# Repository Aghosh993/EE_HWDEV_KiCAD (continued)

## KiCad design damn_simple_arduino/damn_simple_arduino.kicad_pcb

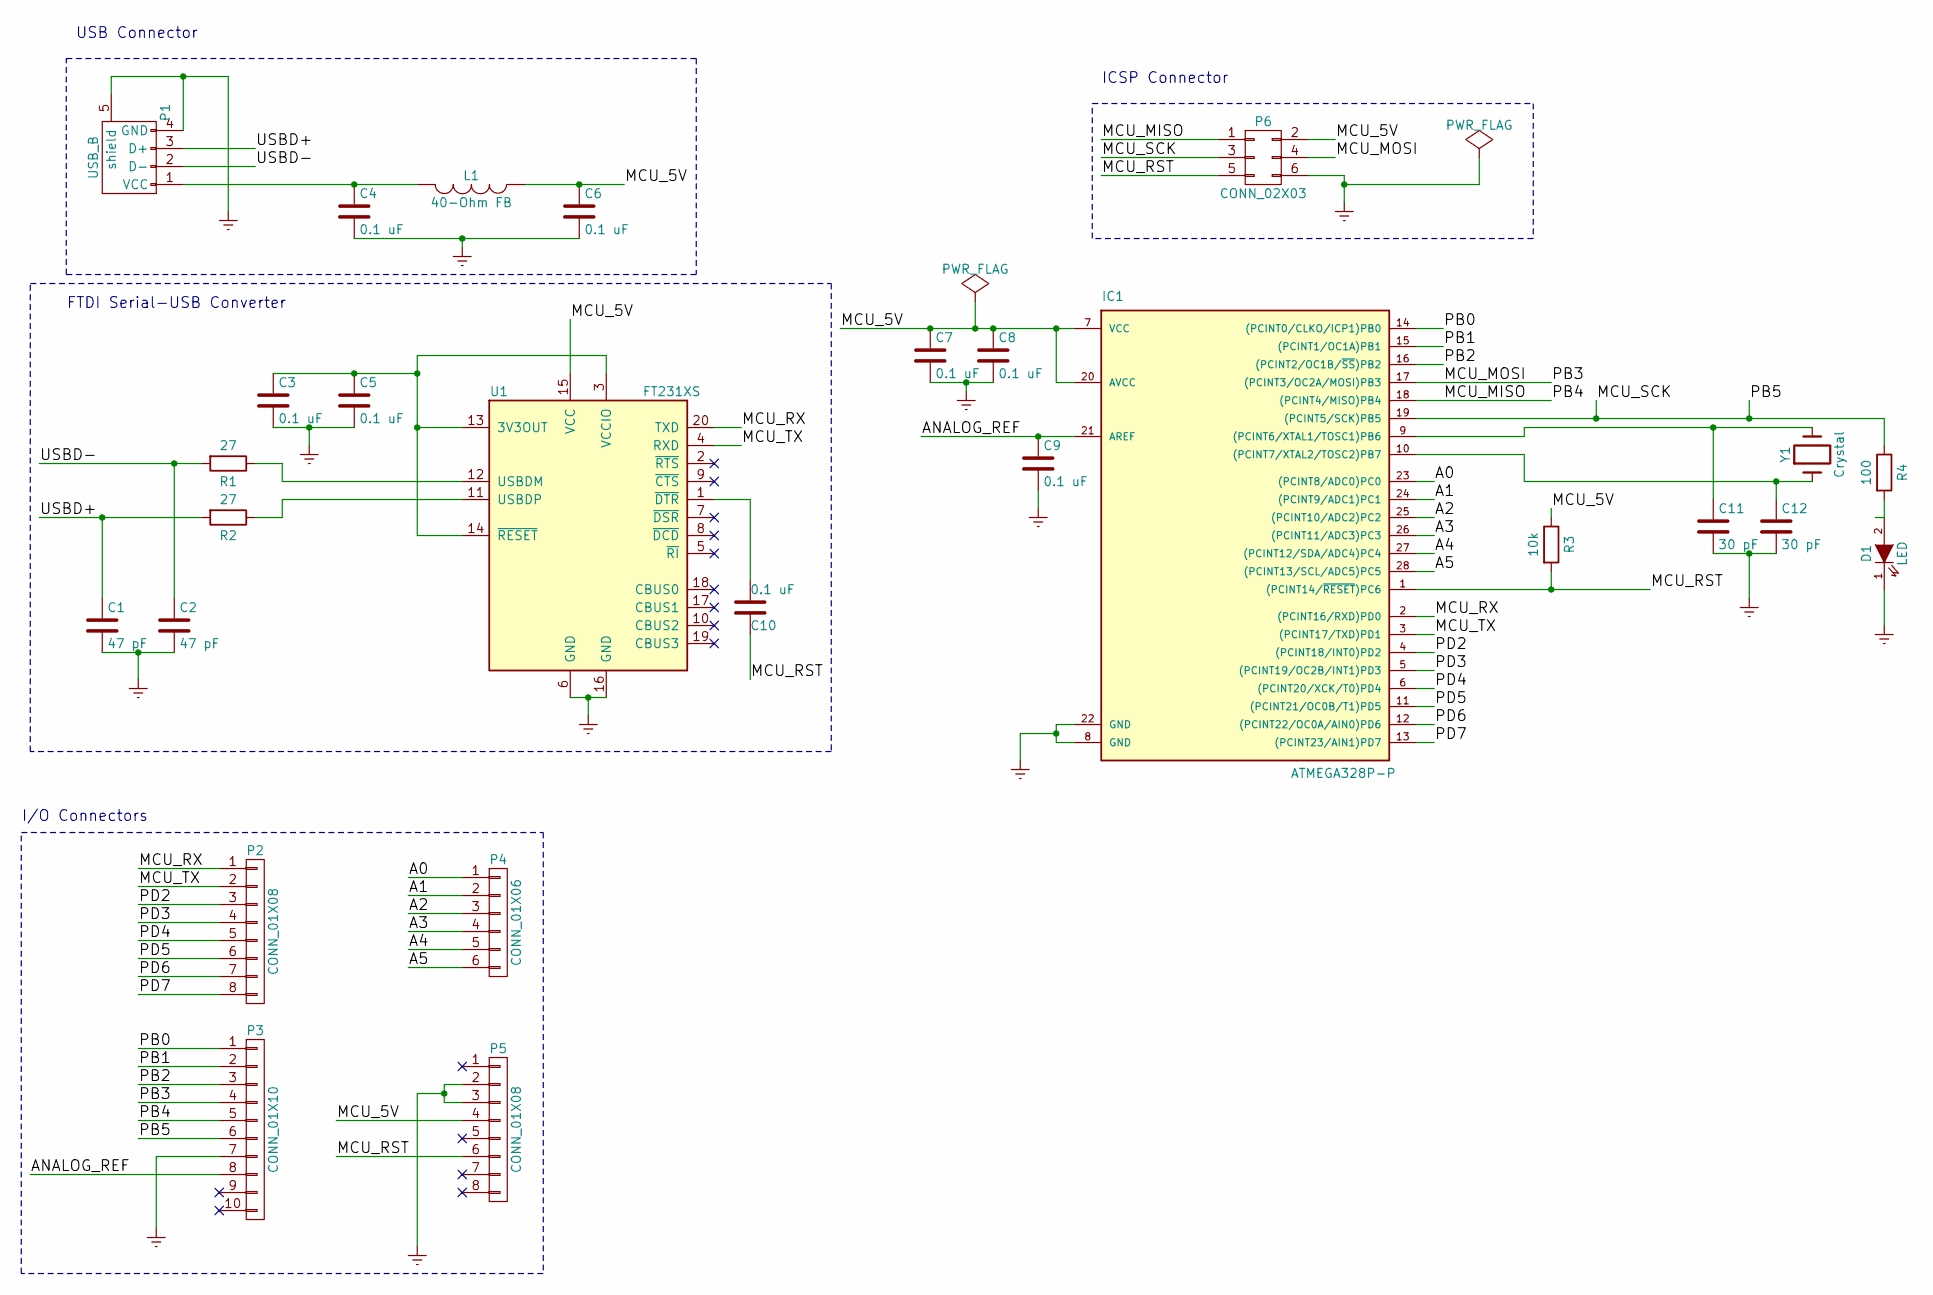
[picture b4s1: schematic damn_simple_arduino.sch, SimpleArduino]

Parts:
C1, C2: 47 pF; C_0603_HandSoldering
C3, C4, C5, C6, C7, C8, C9, C10: 0.1 uF; C_0603_HandSoldering
C11, C12: 30 pF; C_0402
D1: LED; LED-5MM
IC1: ATMEGA328P-P; DIP-28_W7.62mm
L1: 40-Ohm FB; C_0805_HandSoldering
P1: USB_B
P2, P5: CONN_01X08; Pin_Header_Straight_1x08
P3: CONN_01X10; Pin_Header_Straight_1x10
P4: CONN_01X06; Pin_Header_Straight_1x06
P6: CONN_02X03; Pin_Header_Straight_2x03
R1, R2: 27; R_0603_HandSoldering
R3: 10k; R_0603_HandSoldering
R4: 100; R_0603_HandSoldering
U1: FT231XS; SSOP-20-8.66x3.91_0.635mm
Y1: Crystal; Crystal_HC49-U_Vertical

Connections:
/A0: IC1.23 ((PCINT8/ADC0)PC0), P4.1
/A1: IC1.24 ((PCINT9/ADC1)PC1), P4.2
/A2: IC1.25 ((PCINT10/ADC2)PC2), P4.3
/A3: IC1.26 ((PCINT11/ADC3)PC3), P4.4
/A4: IC1.27 ((PCINT12/SDA/ADC4)PC4), P4.5
/A5: IC1.28 ((PCINT13/SCL/ADC5)PC5), P4.6
/ANALOG_REF: C9.1, IC1.21 (AREF), P3.8
/MCU_5V: C6.1, C7.1, C8.1, IC1.7 (VCC), IC1.20 (AVCC), L1.1, P5.4, P6.2, R3.1, U1.15 (VCC)
/MCU_MISO: IC1.18 ((PCINT4/MISO)PB4), P3.5, P6.1
/MCU_MOSI: IC1.17 ((PCINT3/OC2A/MOSI)PB3), P3.4, P6.4
/MCU_RST: C10.1, IC1.1 ((PCINT14/~RESET~)PC6), P5.6, P6.5, R3.2
/MCU_RX: IC1.2 ((PCINT16/RXD)PD0), P2.1, U1.20 (TXD)
/MCU_SCK: IC1.19 ((PCINT5/SCK)PB5), P3.6, P6.3, R4.1
/MCU_TX: IC1.3 ((PCINT17/TXD)PD1), P2.2, U1.4 (RXD)
/PB0: IC1.14 ((PCINT0/CLKO/ICP1)PB0), P3.1
/PB1: IC1.15 ((PCINT1/OC1A)PB1), P3.2
/PB2: IC1.16 ((PCINT2/OC1B/~SS~)PB2), P3.3
/PD2: IC1.4 ((PCINT18/INT0)PD2), P2.3
/PD3: IC1.5 ((PCINT19/OC2B/INT1)PD3), P2.4
/PD4: IC1.6 ((PCINT20/XCK/T0)PD4), P2.5
/PD5: IC1.11 ((PCINT21/OC0B/T1)PD5), P2.6
/PD6: IC1.12 ((PCINT22/OC0A/AIN0)PD6), P2.7
/PD7: IC1.13 ((PCINT23/AIN1)PD7), P2.8
/USBD+: C1.1, P1.3 (D+), R2.2
/USBD-: C2.1, P1.2 (D-), R1.2
Earth: C1.2, C2.2, C3.2, C4.2, C5.2, C6.2, C7.2, C8.2, C9.2, C11.2, C12.2, D1.1 (K), IC1.8 (GND), IC1.22 (GND), P1.4 (GND), P1.5 (shield), P3.7, P5.2, P5.3, P6.6, U1.6 (GND), U1.16 (GND)
unnamed: C3.1, C5.1, U1.3 (VCCIO), U1.13 (3V3OUT), U1.14 (~RESET)
unnamed: C4.1, L1.2, P1.1 (VCC)
unnamed: C10.2, U1.1 (~DTR)
unnamed: C11.1, IC1.9 ((PCINT6/XTAL1/TOSC1)PB6), Y1.2
unnamed: C12.1, IC1.10 ((PCINT7/XTAL2/TOSC2)PB7), Y1.1
unnamed: D1.2 (A), R4.2
unnamed: R1.1, U1.12 (USBDM)
unnamed: R2.1, U1.11 (USBDP)

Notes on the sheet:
ICSP Connector
USB Connector
FTDI Serial-USB Converter
I/O Connectors

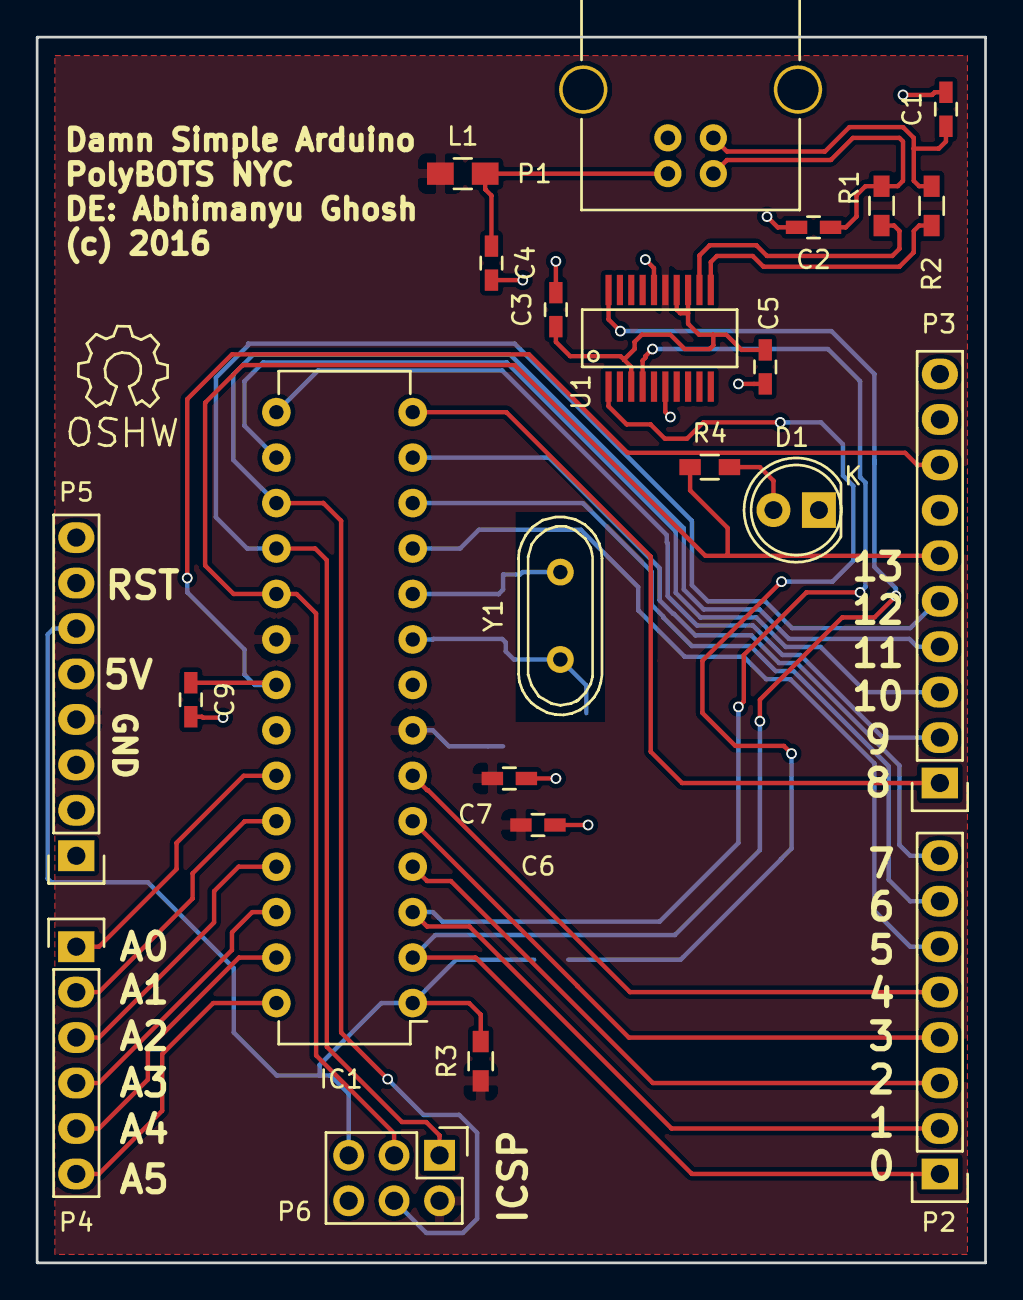
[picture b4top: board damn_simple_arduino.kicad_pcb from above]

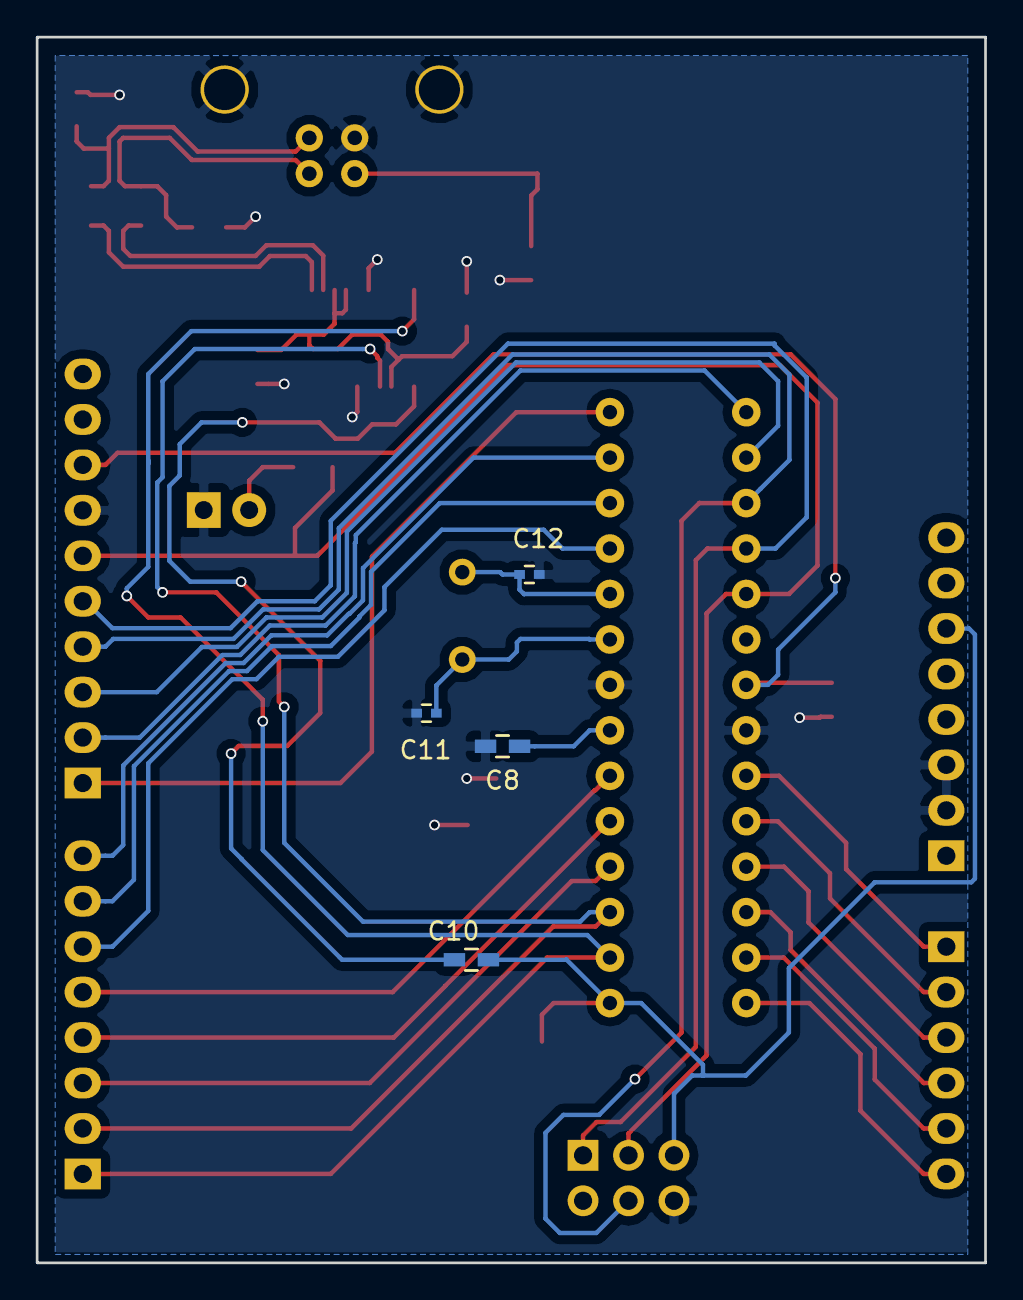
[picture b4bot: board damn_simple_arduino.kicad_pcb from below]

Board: 2 copper layers, 53.0 x 68.5 mm, 27 parts (4 on the bottom side), 34 nets.

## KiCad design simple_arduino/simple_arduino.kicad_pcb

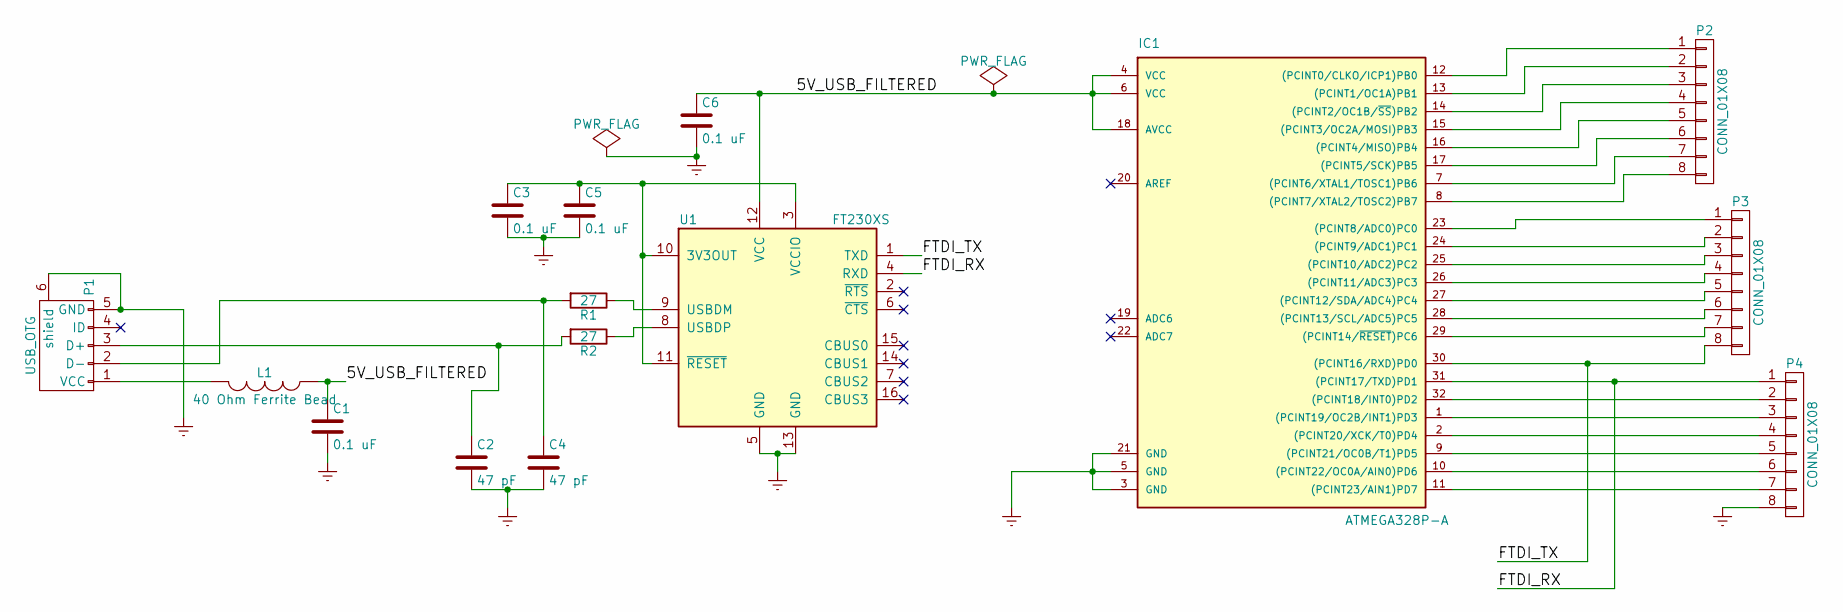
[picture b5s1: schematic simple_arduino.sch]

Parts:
C1, C3, C5, C6: 0.1 uF; C_0603_HandSoldering
C2, C4: 47 pF; C_0603_HandSoldering
IC1: ATMEGA328P-A; TQFP-32_7x7mm_Pitch0.8mm
L1: 40 Ohm Ferrite Bead; C_0805_HandSoldering
P1: USB_OTG; USB_Micro-B
P2, P3, P4: CONN_01X08; Socket_Strip_Straight_1x08
R1, R2: 27; R_0603_HandSoldering
U1: FT230XS; SSOP-16_3.9x4.9mm_Pitch0.635mm

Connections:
/5V_USB_FILTERED: C1.1, C6.1, IC1.4 (VCC), IC1.6 (VCC), IC1.18 (AVCC), L1.1, U1.12 (VCC)
/FTDI_RX: IC1.31 ((PCINT17/TXD)PD1), P4.1, U1.4 (RXD)
/FTDI_TX: IC1.30 ((PCINT16/RXD)PD0), P3.8, U1.1 (TXD)
Earth: C1.2, C2.2, C3.2, C4.2, C5.2, C6.2, IC1.3 (GND), IC1.5 (GND), IC1.21 (GND), P1.5 (GND), P1.6 (shield), P4.8, U1.5 (GND), U1.13 (GND)
unnamed: C2.1, P1.3 (D+), R2.2
unnamed: C3.1, C5.1, U1.3 (VCCIO), U1.10 (3V3OUT), U1.11 (~RESET)
unnamed: C4.1, P1.2 (D-), R1.2
unnamed: IC1.1 ((PCINT19/OC2B/INT1)PD3), P4.3
unnamed: IC1.2 ((PCINT20/XCK/T0)PD4), P4.4
unnamed: IC1.7 ((PCINT6/XTAL1/TOSC1)PB6), P2.7
unnamed: IC1.8 ((PCINT7/XTAL2/TOSC2)PB7), P2.8
unnamed: IC1.9 ((PCINT21/OC0B/T1)PD5), P4.5
unnamed: IC1.10 ((PCINT22/OC0A/AIN0)PD6), P4.6
unnamed: IC1.11 ((PCINT23/AIN1)PD7), P4.7
unnamed: IC1.12 ((PCINT0/CLKO/ICP1)PB0), P2.1
unnamed: IC1.13 ((PCINT1/OC1A)PB1), P2.2
unnamed: IC1.14 ((PCINT2/OC1B/~SS~)PB2), P2.3
unnamed: IC1.15 ((PCINT3/OC2A/MOSI)PB3), P2.4
unnamed: IC1.16 ((PCINT4/MISO)PB4), P2.5
unnamed: IC1.17 ((PCINT5/SCK)PB5), P2.6
unnamed: IC1.23 ((PCINT8/ADC0)PC0), P3.1
unnamed: IC1.24 ((PCINT9/ADC1)PC1), P3.2
unnamed: IC1.25 ((PCINT10/ADC2)PC2), P3.3
unnamed: IC1.26 ((PCINT11/ADC3)PC3), P3.4
unnamed: IC1.27 ((PCINT12/SDA/ADC4)PC4), P3.5
unnamed: IC1.28 ((PCINT13/SCL/ADC5)PC5), P3.6
unnamed: IC1.29 ((PCINT14/~RESET~)PC6), P3.7
unnamed: IC1.32 ((PCINT18/INT0)PD2), P4.2
unnamed: L1.2, P1.1 (VCC)
unnamed: R1.1, U1.9 (USBDM)
unnamed: R2.1, U1.8 (USBDP)

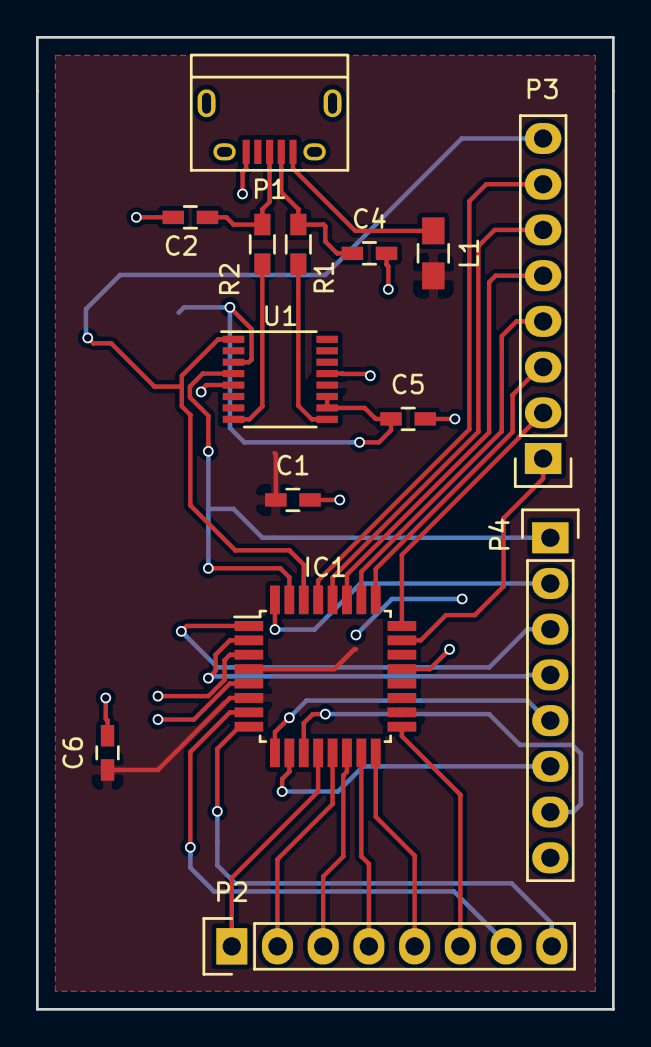
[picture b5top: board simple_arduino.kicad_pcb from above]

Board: 2 copper layers, 32.0 x 54.0 mm, 15 parts (1 on the bottom side), 31 nets.

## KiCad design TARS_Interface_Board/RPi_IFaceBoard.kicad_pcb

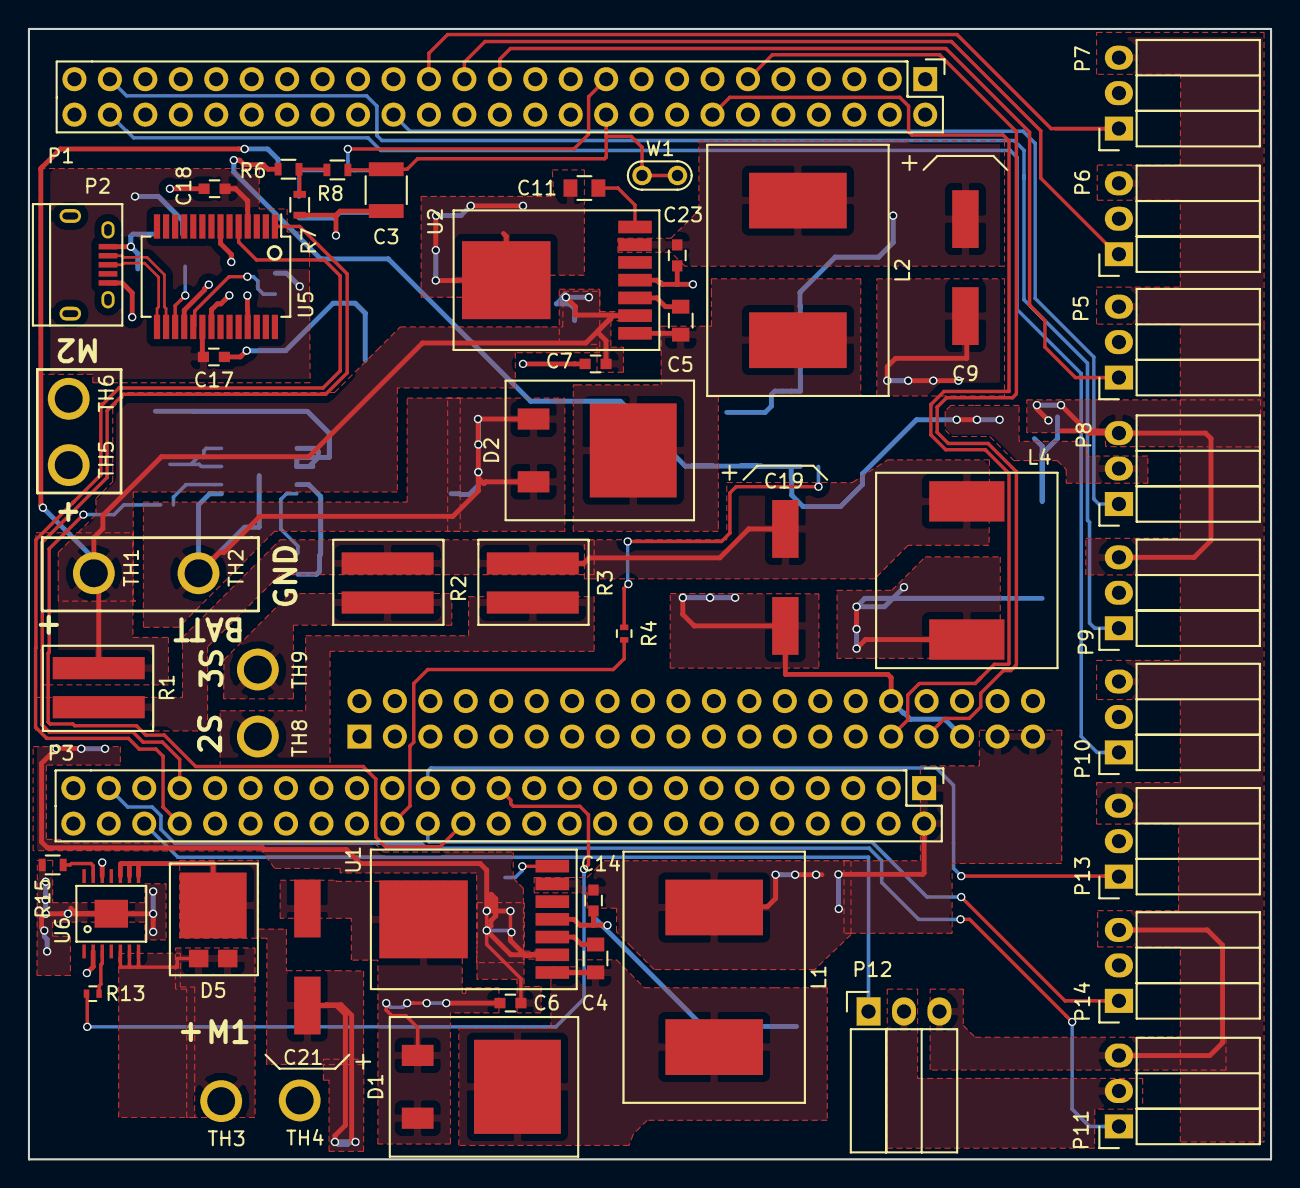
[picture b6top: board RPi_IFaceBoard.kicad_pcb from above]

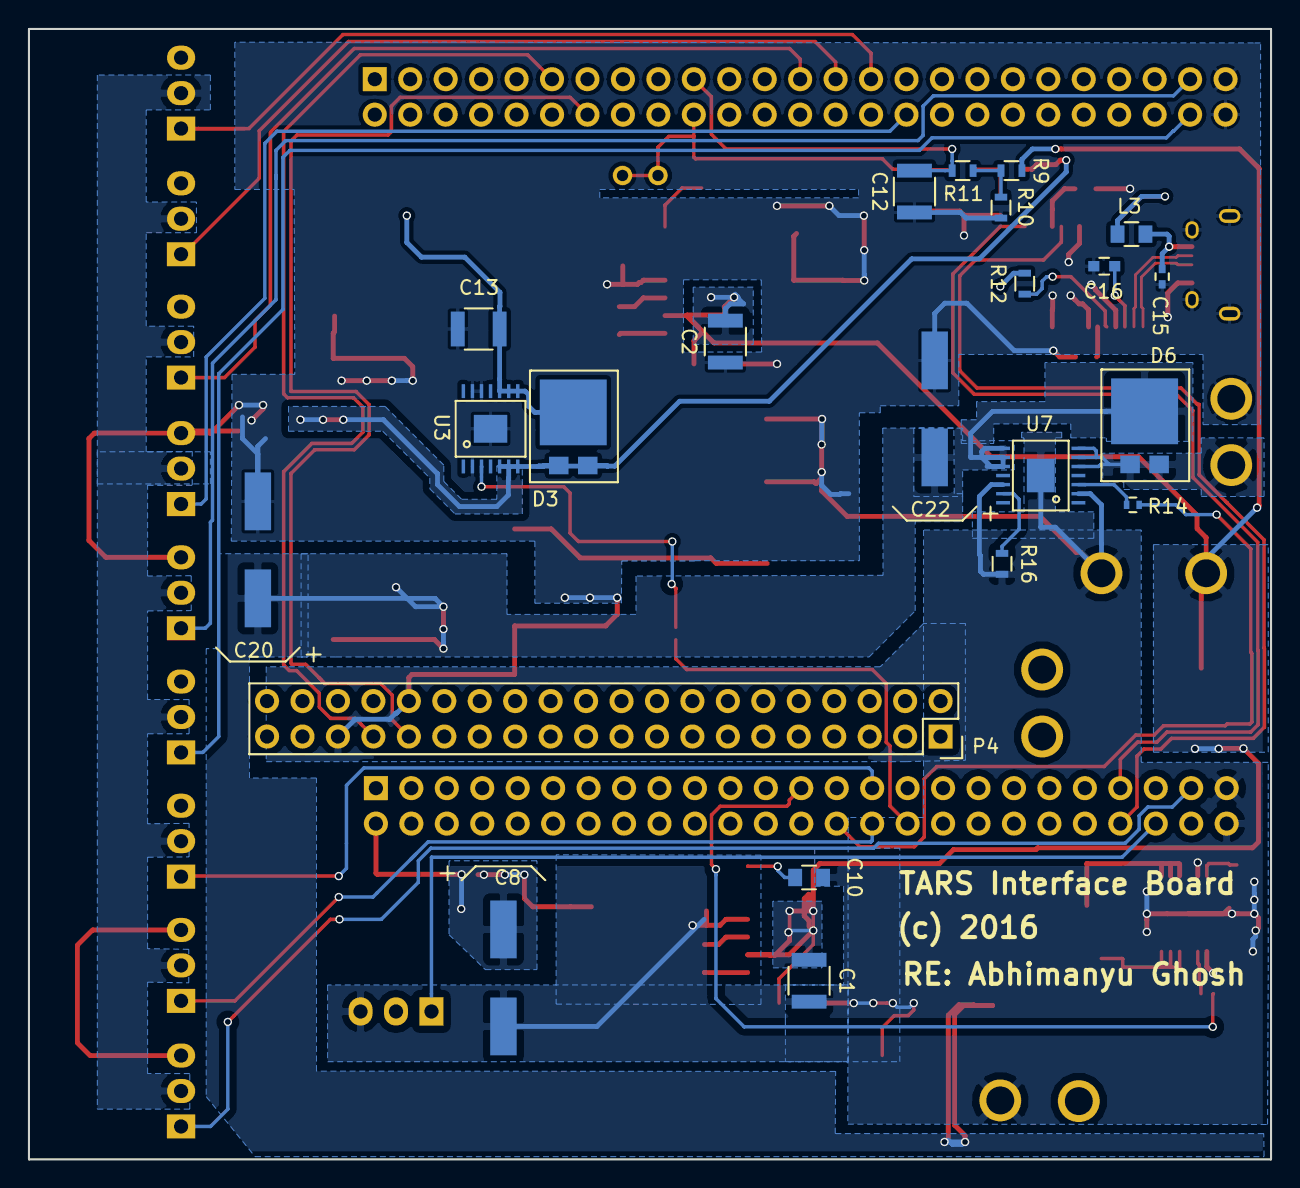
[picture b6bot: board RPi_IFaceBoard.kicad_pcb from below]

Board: 2 copper layers, 89.0 x 81.0 mm, 76 parts (22 on the bottom side), 49 nets.

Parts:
C1, C2, C3, C12, C13: 10 uF; C_1210
C4, C5: 10 nF; C_0805
C6, C7, C14, C23: 1.0 uF; C_0603
C8, C9, C21, C22: 120 uF; Radial_SMD_8mm
C10, C11: 0.27 uF; C_0805
C15: 10 nF; C_0402
C16, C17, C18: 0.1 uF; C_0603
C19, C20: 82 uF; Radial_SMD_8mm
D1, D2: Vrrm=40.0V,Vf=510.0 mV; DPAK_TO252AA_CUSTOM
D3, D5, D6: SCHDPAK; TO277A
L1, L2: 6.5 uH, 18 mOhm; SRR1208
L3: 40 Ohm FB; C_0805
L4: 15 uH; INDUCTOR_SMD_WURTH_5.4X2.9PADS_9.9SPACE
P1, P3: CONN_02X25; Socket_Strip_Straight_2x25
P2: USB_OTG; USB_Micro-B
P4: CONN_02X20; Socket_Strip_Straight_2x20
P5, P6, P7, P8, P9, P10, P11, P12, P13, P14: CONN_01X03; Socket_Strip_Angled_1x03
R1: 0; RES_RCL1225
R2, R3: 0 DNP; RES_RCL1225
R4, R13, R14: 3.3K; R_0402
R6: 2.2K; R_0603
R7, R10: 1.1K; R_0603
R8, R11: 100; R_0603
R9: 6.65K; R_0603
R12: 10K; R_0603
R15, R16: 499; R_0603
TH1, TH2, TH3, TH4, TH5, TH6, TH8, TH9: PTH
U1, U2: LM22679; TI_TO-263
U3, U6, U7: TPS1H100AQPWPRQ1; PowerPAD_14pin_EP
U5: FT232RL; SSOP-28_5.3x10.2mm_Pitch0.65mm
W1: TEST_1P; Test_Point

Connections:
+5V: C8.1, C14.1, L1.2, P3.1, P3.2, P4.37, P4.39, U1.6
/DCMotor_Quarter_HBridges/AS_PWR: C19.1, L4.2, R1.1, R2.1, R3.1
/DCMotor_Quarter_HBridges/MOTOR0_OUT: D5.1, D5.3, TH3.1, U6.5, U6.6, U6.7
/DCMotor_Quarter_HBridges/MOTOR0_PWM: P3.25, R13.2
/DCMotor_Quarter_HBridges/MOTOR1_OUT: D6.1, D6.3, TH5.1, U7.5, U7.6, U7.7
/DCMotor_Quarter_HBridges/MOTOR1_PWM: P3.28, R14.2
/DCMotor_Quarter_HBridges/VBAT_FLT: C20.1, C21.1, C22.1, D5.2, D6.2, L4.1, U6.8, U6.9, U6.10, U7.8, U7.9, U7.10
/DebugFTDI/RX: P3.44, U5.5
/DebugFTDI/TX: P3.43, U5.1
/DebugFTDI/USBD+: P2.3, U5.15
/DebugFTDI/USBD-: P2.2, U5.16
/DebugFTDI/VUSB: C15.1, L3.2, P2.1
/DebugFTDI/VUSB_FLT: C17.1, C18.1, L3.1, R12.2, U5.4, U5.20
/PWM0: P1.25, P5.1
/PWM1: P1.27, P6.1
/PWM2: P1.29, P7.1
/PWM3: P1.32, P8.1
/PWM4: P1.47, P9.1
/PWM5: P1.48, P10.1
/PWM6: P3.47, P11.1
/PWM7: P3.46, P12.1
/PWM8: P3.29, P13.1
/PWM9: P3.30, P14.1
/PowerSupplies/SERVO_PWR_EN: P3.32, R4.2
/PowerSupplies/SERVO_PWR_FB: C3.1, P1.20, R8.1, W1.1
/PowerSupplies/SRV_5V_OUT: D3.1, D3.3, P5.2, P6.2, P7.2, P8.2, P9.2, P10.2, P11.2, P12.2, P13.2, P14.2, R6.1, U3.5, U3.6, U3.7
/PowerSupplies/SRV_5V_SW_UPSTREAM: C9.1, C13.1, C23.1, D3.2, L2.2, U2.6, U3.8, U3.9, U3.10
/PowerSupplies/SW_OUT: C4.2, D1.1, L1.1, U1.1
/PowerSupplies/SW_OUT2: C5.2, D2.1, L2.1, U2.1
/PowerSupplies/VBAT: C1.1, C2.1, C6.1, C7.1, R1.2, R9.1, TH1.1, U1.2, U2.2
/PowerSupplies/VBAT_FB: C12.1, P1.19, R11.1
/RX_PI: P1.11, P4.33
/TX_PI: P1.14, P4.31
/VBAT_2S: R3.2, TH8.1
/VBAT_3S: R2.2, TH9.1
Earth: C1.2, C2.2, C3.2, C6.2, C7.2, C8.2, C9.2, C10.2, C11.2, C12.2, C13.2, C14.2, C15.2, C16.2, C17.2, C18.2, C19.2, C20.2, C21.2, C22.2, C23.2, D1.2, D2.2, P1.49, P1.50, P2.5, P2.6, P3.49, P3.50, P4.32, P4.35, P5.3, P6.3, P7.3, P8.3, P9.3, P10.3, P11.3, P12.3, P13.3, P14.3, R7.2, R10.2, R15.2, R16.2, TH2.1, TH4.1, TH6.1, U1.4, U1.8, U2.4, U2.8, U3.2, U3.12, U3.13, U5.7, U5.18, U5.21, U5.25, U6.2, U6.12, U7.2, U7.12
unnamed: C4.1, U1.3
unnamed: C5.1, U2.3
unnamed: C10.1, U1.7
unnamed: C11.1, U2.7
unnamed: C16.1, U5.17
unnamed: R4.1, U3.3
unnamed: R6.2, R7.1, R8.2
unnamed: R9.2, R10.1, R11.2
unnamed: R12.1, U5.19
unnamed: R13.1, U6.3
unnamed: R14.1, U7.3
unnamed: R15.1, U6.13
unnamed: R16.1, U7.13

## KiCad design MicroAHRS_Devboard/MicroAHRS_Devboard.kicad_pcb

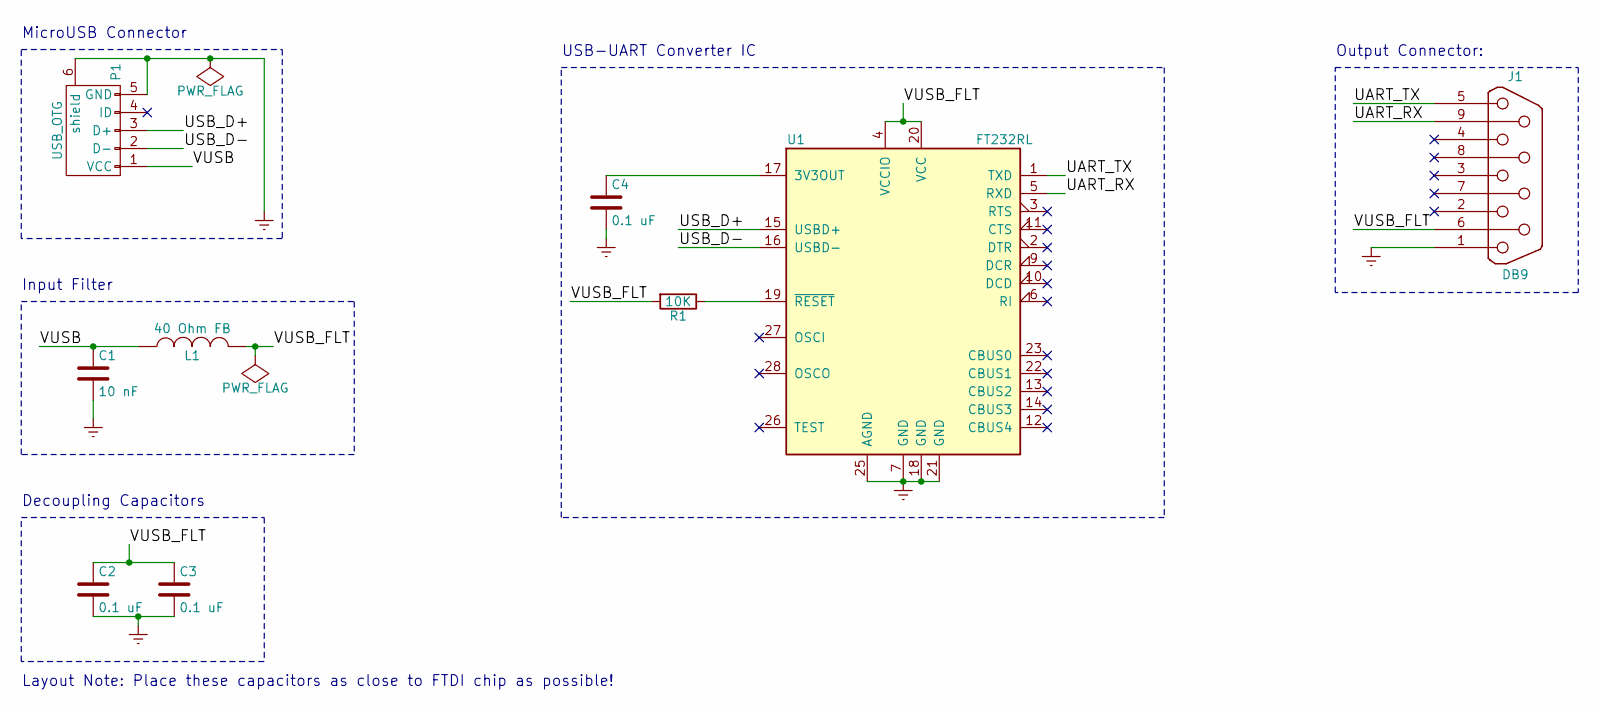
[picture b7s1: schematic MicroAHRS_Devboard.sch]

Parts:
C1: 10 nF; C_0402
C2, C3, C4: 0.1 uF; C_0603
J1: DB9; DB9MC
L1: 40 Ohm FB; C_0805
P1: USB_OTG; USB_Micro-B
R1: 10K; R_0603
U1: FT232RL; SSOP-28_5.3x10.2mm_Pitch0.65mm

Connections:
/UART_RX: J1.9, U1.5 (RXD)
/UART_TX: J1.5, U1.1 (TXD)
/USB_D+: P1.3 (D+), U1.15 (USBD+)
/USB_D-: P1.2 (D-), U1.16 (USBD-)
/VUSB: C1.1, L1.1, P1.1 (VCC)
/VUSB_FLT: C2.1, C3.1, J1.6, L1.2, R1.2, U1.4 (VCCIO), U1.20 (VCC)
Earth: C1.2, C2.2, C3.2, C4.2, J1.1, P1.5 (GND), P1.6 (shield), U1.7 (GND), U1.18 (GND), U1.21 (GND), U1.25 (AGND)
unnamed: C4.1, U1.17 (3V3OUT)
unnamed: R1.1, U1.19 (~RESET~)

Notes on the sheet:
MicroUSB Connector
Input Filter
Decoupling Capacitors
Layout Note: Place these capacitors as close to FTDI chip as possible!
Output Connector:
USB-UART Converter IC

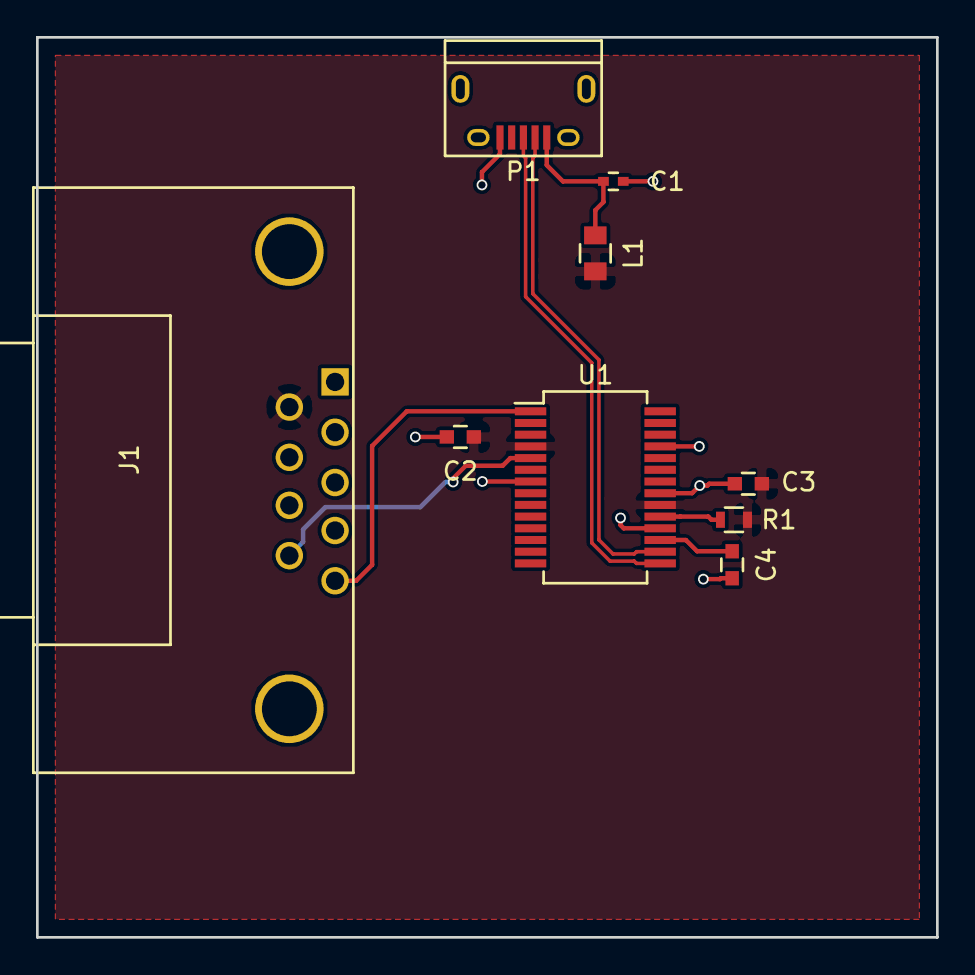
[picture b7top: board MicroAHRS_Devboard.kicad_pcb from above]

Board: 2 copper layers, 50.0 x 50.0 mm, 9 parts (0 on the bottom side), 9 nets.

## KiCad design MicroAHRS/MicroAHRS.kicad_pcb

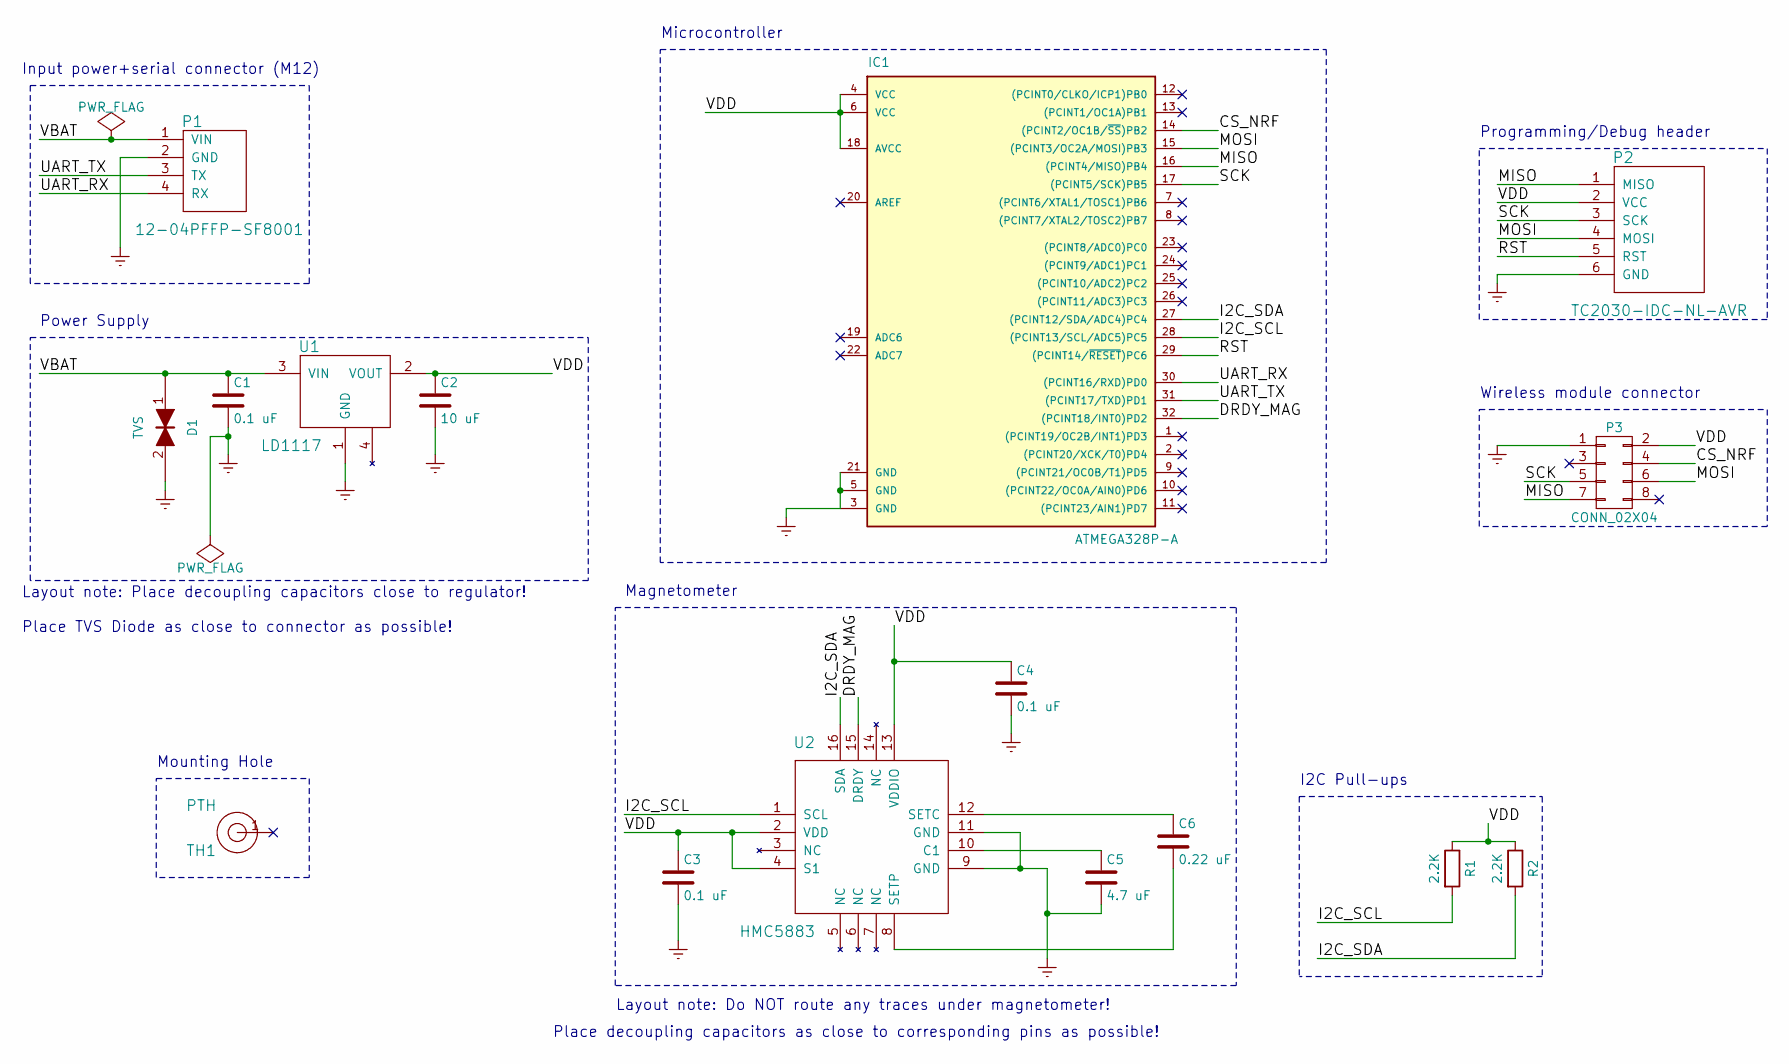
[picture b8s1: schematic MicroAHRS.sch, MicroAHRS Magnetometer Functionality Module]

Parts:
C1, C3, C4: 0.1 uF; C_0402
C2: 10 uF; C_0805
C5: 4.7 uF; C_1210
C6: 0.22 uF; C_0402
D1: TVS; TVS_0603
IC1: ATMEGA328P-A; TQFP-32_7x7mm_Pitch0.8mm
P1: 12-04PFFP-SF8001
P2: TC2030-IDC-NL-AVR
P3: CONN_02X04; Socket_Strip_Straight_2x04
R1, R2: 2.2K; R_0603
TH1: PTH; MountingHole_3mm
U1: LD1117; SOT-223
U2: HMC5883; LCC16

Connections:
/CS_NRF: IC1.14 ((PCINT2/OC1B/~SS~)PB2), P3.4
/DRDY_MAG: IC1.32 ((PCINT18/INT0)PD2), U2.15 (DRDY)
/I2C_SCL: IC1.28 ((PCINT13/SCL/ADC5)PC5), R1.2, U2.1 (SCL)
/I2C_SDA: IC1.27 ((PCINT12/SDA/ADC4)PC4), R2.2, U2.16 (SDA)
/MISO: IC1.16 ((PCINT4/MISO)PB4), P2.1 (MISO), P3.7
/MOSI: IC1.15 ((PCINT3/OC2A/MOSI)PB3), P2.4 (MOSI), P3.6
/RST: IC1.29 ((PCINT14/~RESET~)PC6), P2.5 (RST)
/SCK: IC1.17 ((PCINT5/SCK)PB5), P2.3 (SCK), P3.5
/UART_RX: IC1.30 ((PCINT16/RXD)PD0), P1.4 (RX)
/UART_TX: IC1.31 ((PCINT17/TXD)PD1), P1.3 (TX)
/VBAT: C1.1, D1.1, P1.1 (VIN), U1.3 (VIN)
/VDD: C2.1, C3.1, C4.1, IC1.4 (VCC), IC1.6 (VCC), IC1.18 (AVCC), P2.2 (VCC), P3.2, R1.1, R2.1, U1.2 (VOUT), U2.2 (VDD), U2.4 (S1), U2.13 (VDDIO)
Earth: C1.2, C2.2, C3.2, C4.2, C5.2, D1.2, IC1.3 (GND), IC1.5 (GND), IC1.21 (GND), P1.2 (GND), P2.6 (GND), P3.1, U1.1 (GND), U2.9 (GND), U2.11 (GND)
unnamed: C5.1, U2.10 (C1)
unnamed: C6.1, U2.12 (SETC)
unnamed: C6.2, U2.8 (SETP)

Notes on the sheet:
Input power+serial connector (M12)
Power Supply
Layout note: Place decoupling capacitors close to regulator! Place TVS Diode as close to connector as possible!
Layout note: Do NOT route any traces under magnetometer!
Place decoupling capacitors as close to corresponding pins as possible!
I2C Pull-ups
Magnetometer
Programming/Debug header
Wireless module connector
Microcontroller
Mounting Hole

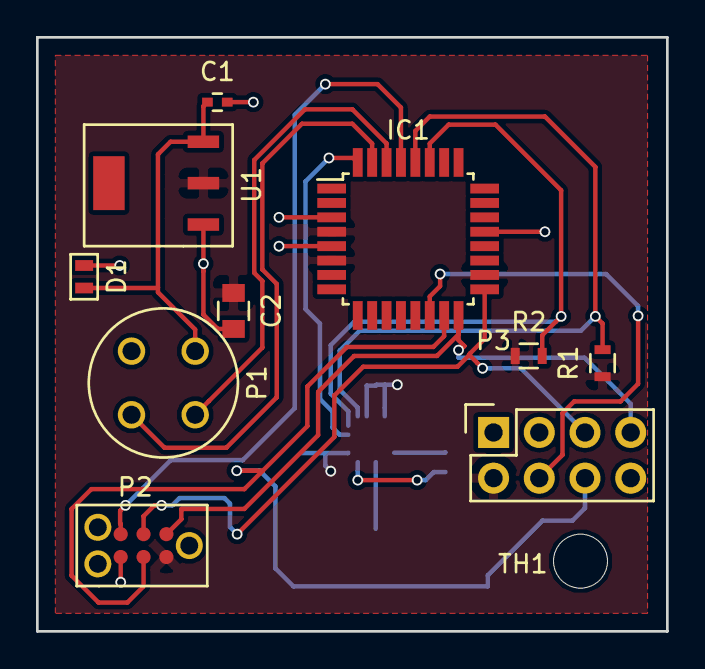
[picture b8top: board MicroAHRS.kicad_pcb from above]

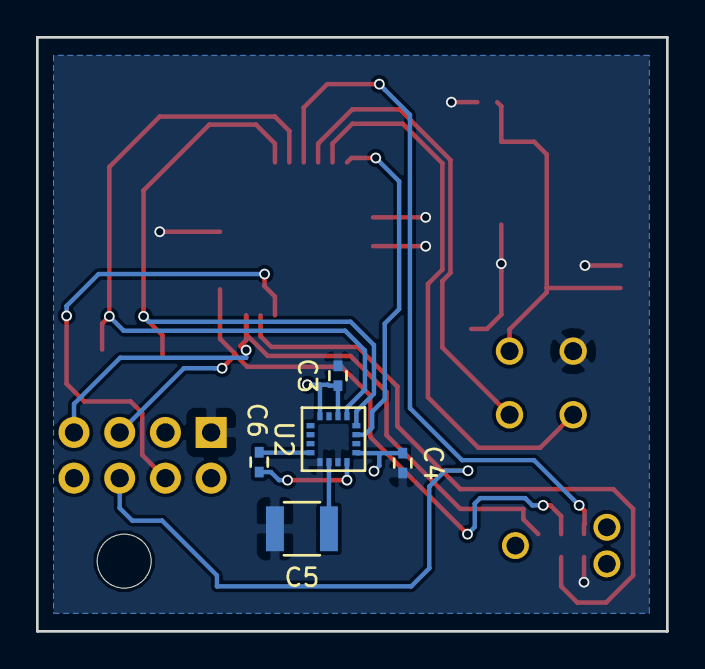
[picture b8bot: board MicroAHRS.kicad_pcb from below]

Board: 2 copper layers, 35.0 x 33.0 mm, 16 parts (5 on the bottom side), 16 nets.

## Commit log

2016-11-25 Adding simple Arduino for PolyBOTS workshop.
2016-11-25 Pushing latest 3D renders and current working view.
2016-11-25 Adding PDF plot of schematic.
2016-11-25 Adding simple Arduino clone from Advanced KiCAD workshop a few weeks ago.
2016-12-02 Updating design to AC couple the reset line to DTR, after bring-up tests.
2016-12-02 Updating layout with keepout zone for crystal. Also adding BOM.
2016-12-02 Adding scripts to build OSHPark fab files. Also a few layout mods.
2017-02-24 Adding RoboBoard.
2017-02-27 Updating to latest rev as ordered on OSHPark.
2017-03-20 Adding Unified Quadcopter Power Distribution Board.
2017-03-20 Adding STM32 interface board.
2017-03-21 Fixing DRC issues.
2017-03-22 Updating PDB to fix clearance issue.
2017-04-05 Adding schematics for Dev0_1 initial edition of STM32 Interface Board for Embedded Systems course.
2017-04-05 Adding build errata to STM32 interface board.
2017-04-05 Adding latest STM32 Interface board files.
2017-04-05 Adding latest schematics and clarifications.
2017-04-05 Adding ICD for STM32 Interface Board.
2017-04-05 Updating ICD.
2017-04-05 Adding Release ICD.
2017-04-06 Updating STM Interface board to latest rev.
2017-04-06 Correcting screenshot
2017-05-26 Updating silkscreen on Quadcopter PDB.
2017-05-31 Updating Quadcopter PDB to latest combined design capable of accomodating AP or STM32 systems.
2017-05-31 One last update.
